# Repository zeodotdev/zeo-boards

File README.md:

# Zeo Boards

This is a repo of boards made with zeo made by the team and submitted by users.

- demo_board: The board made in the [walkthrough](https://youtu.be/U7OuzNha7m4?si=L84EUU4cbVrLih4U)
- zeo1_debvoard: 1inx1in sensor board built on the esp32c3: placed with ai + autorouted
- jared_tv_remote: Jared's universal TV remote, codename: "Bromote 9000"
- fpv_drone: PCB drone frame designed for DL2205-2300KV Motors. placed by hand + routed by hand
- zeo1.2_devboard: a more powerful 1inx1in sensor board build built on the esp32s3: placed + routed by hand
- zeo_compute_module: a compute module designed arounf the RK3588, in-progress

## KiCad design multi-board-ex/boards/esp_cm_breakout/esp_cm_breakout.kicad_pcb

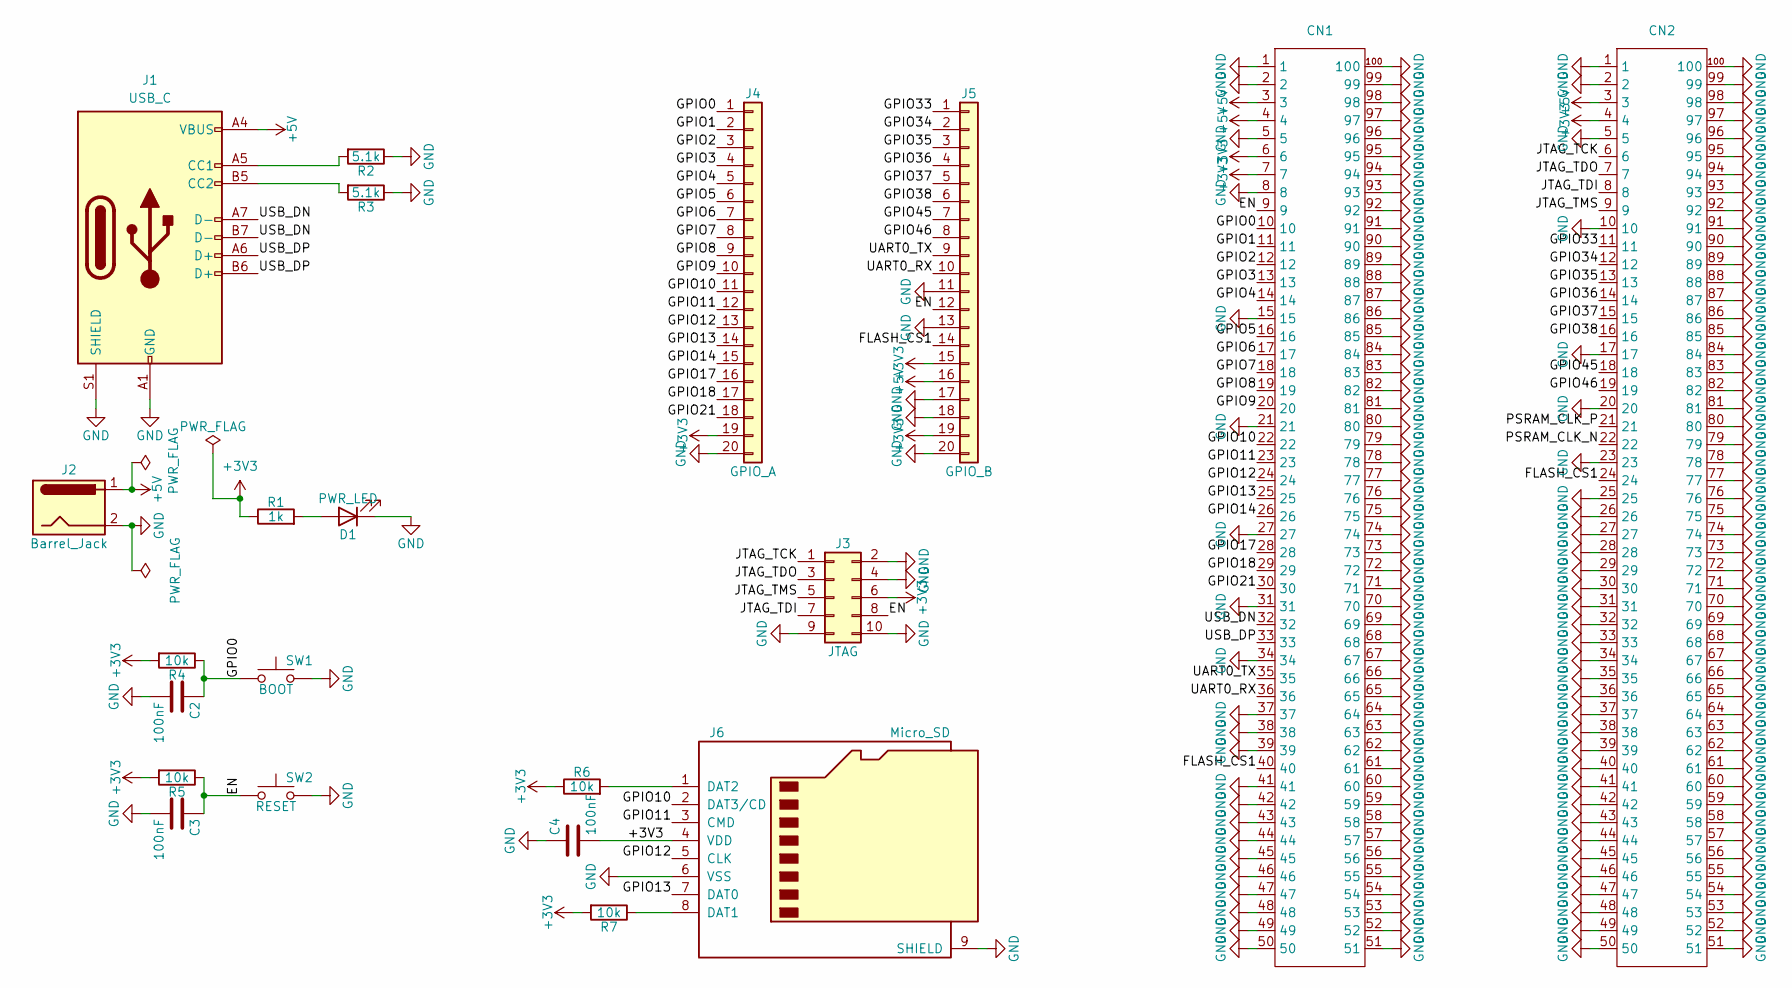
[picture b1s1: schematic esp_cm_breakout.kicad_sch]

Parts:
C2, C3, C4: 100nF; C_0603_1608Metric
CN1, CN2: CONN-SMD_DF40C-100DS-0.4V-51; Manufacturer Part DF40C-100DS-0.4V(51); LCSC Part Name PIN:100P 间距:0.4mm 立贴
D1: PWR_LED; LED_0603_1608Metric
J1: USB_C; USB_C_Receptacle_GCT_USB4085
J2: Barrel_Jack; BarrelJack_Horizontal
J3: JTAG; PinHeader_2x05_P2.54mm_Vertical
J4: GPIO_A; PinHeader_1x20_P2.54mm_Vertical
J5: GPIO_B; PinHeader_1x20_P2.54mm_Vertical
J6: Micro_SD; microSD_HC_Wuerth_693072010801
R1: 1k; R_0603_1608Metric
R2, R3: 5.1k; R_0603_1608Metric
R4, R5, R6, R7: 10k; R_0603_1608Metric
SW1: BOOT; SW_PUSH_6mm
SW2: RESET; SW_PUSH_6mm

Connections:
+3V3: C4.2, CN1.6, CN1.7, CN2.4, J3.6, J4.19, J5.15, J5.19, J6.4 (VDD_4), R1.1, R4.2, R5.2, R6.1, R7.2
+5V: CN1.3, CN1.4, CN2.3, J1.A4 (VBUS), J1.A9 (VBUS), J1.B4 (VBUS), J1.B9 (VBUS), J2.1, J5.16
/EN: C3.1, CN1.9, J3.8, J5.12, R5.1, SW2.1
/FLASH_CS1: CN1.40, CN2.24, J5.14
/GPIO0: C2.1, CN1.10, J4.1, R4.1, SW1.1
/GPIO1: CN1.11, J4.2
/GPIO2: CN1.12, J4.3
/GPIO3: CN1.13, J4.4
/GPIO4: CN1.14, J4.5
/GPIO5: CN1.16, J4.6
/GPIO6: CN1.17, J4.7
/GPIO7: CN1.18, J4.8
/GPIO8: CN1.19, J4.9
/GPIO9: CN1.20, J4.10
/GPIO10: CN1.22, J4.11, J6.2 (DAT3/CD_2)
/GPIO11: CN1.23, J4.12, J6.3 (CMD_3)
/GPIO12: CN1.24, J4.13, J6.5 (CLK_5)
/GPIO13: CN1.25, J4.14, J6.7 (DAT0_7)
/GPIO14: CN1.26, J4.15
/GPIO17: CN1.28, J4.16
/GPIO18: CN1.29, J4.17
/GPIO21: CN1.30, J4.18
/GPIO33: CN2.11, J5.1
/GPIO34: CN2.12, J5.2
/GPIO35: CN2.13, J5.3
/GPIO36: CN2.14, J5.4
/GPIO37: CN2.15, J5.5
/GPIO38: CN2.16, J5.6
/GPIO45: CN2.18, J5.7
/GPIO46: CN2.19, J5.8
/JTAG_TCK: CN2.6, J3.1
/JTAG_TDI: CN2.8, J3.7
/JTAG_TDO: CN2.7, J3.3
/JTAG_TMS: CN2.9, J3.5
/PSRAM_CLK_N: CN2.22
/PSRAM_CLK_P: CN2.21
/UART0_RX: CN1.36, J5.10
/UART0_TX: CN1.35, J5.9
/USB_DN: CN1.32, J1.A7 (D-), J1.B7 (D-)
/USB_DP: CN1.33, J1.A6 (D+), J1.B6 (D+)
GND: C2.2, C3.2, C4.1, CN1.1, CN1.2, CN1.5, CN1.8, CN1.15, CN1.21, CN1.27, CN1.31, CN1.34, CN1.37, CN1.38, CN1.39, CN1.41, CN1.42, CN1.43, CN1.44, CN1.45, CN1.46, CN1.47, CN1.48, CN1.49, CN1.50, CN1.51, CN1.52, CN1.53, CN1.54, CN1.55, CN1.56, CN1.57, CN1.58, CN1.59, CN1.60, CN1.61, CN1.62, CN1.63, CN1.64, CN1.65, CN1.66, CN1.67, CN1.68, CN1.69, CN1.70, CN1.71, CN1.72, CN1.73, CN1.74, CN1.75, CN1.76, CN1.77, CN1.78, CN1.79, CN1.80, CN1.81, CN1.82, CN1.83, CN1.84, CN1.85, CN1.86, CN1.87, CN1.88, CN1.89, CN1.90, CN1.91, CN1.92, CN1.93, CN1.94, CN1.95, CN1.96, CN1.97, CN1.98, CN1.99, CN1.100, CN2.1, CN2.2, CN2.5, CN2.10, CN2.17, CN2.20, CN2.23, CN2.25, CN2.26, CN2.27, CN2.28, CN2.29, CN2.30, CN2.31, CN2.32, CN2.33, CN2.34, CN2.35, CN2.36, CN2.37, CN2.38, CN2.39, CN2.40, CN2.41, CN2.42, CN2.43, CN2.44, CN2.45, CN2.46, CN2.47, CN2.48, CN2.49, CN2.50, CN2.51, CN2.52, CN2.53, CN2.54, CN2.55, CN2.56, CN2.57, CN2.58, CN2.59, CN2.60, CN2.61, CN2.62, CN2.63, CN2.64, CN2.65, CN2.66, CN2.67, CN2.68, CN2.69, CN2.70, CN2.71, CN2.72, CN2.73, CN2.74, CN2.75, CN2.76, CN2.77, CN2.78, CN2.79, CN2.80, CN2.81, CN2.82, CN2.83, CN2.84, CN2.85, CN2.86, CN2.87, CN2.88, CN2.89, CN2.90, CN2.91, CN2.92, CN2.93, CN2.94, CN2.95, CN2.96, CN2.97, CN2.98, CN2.99, CN2.100, D1.1 (K), J1.A1 (GND), J1.A12 (GND), J1.B1 (GND), J1.B12 (GND), J1.S1 (SHIELD), J2.2, J3.2, J3.4, J3.9, J3.10, J4.20, J5.11, J5.13, J5.17, J5.18, J5.20, J6.6 (VSS_6), J6.9 (SHIELD_9), J6.11 (SHIELD_9), R2.1, R3.1, SW1.2, SW2.2
unnamed: D1.2 (A), R1.2
unnamed: J1.A5 (CC1), R2.2
unnamed: J1.B5 (CC2), R3.2
unnamed: J6.8 (DAT1_8), R7.1
unnamed: J6.1 (DAT2_1), R6.2

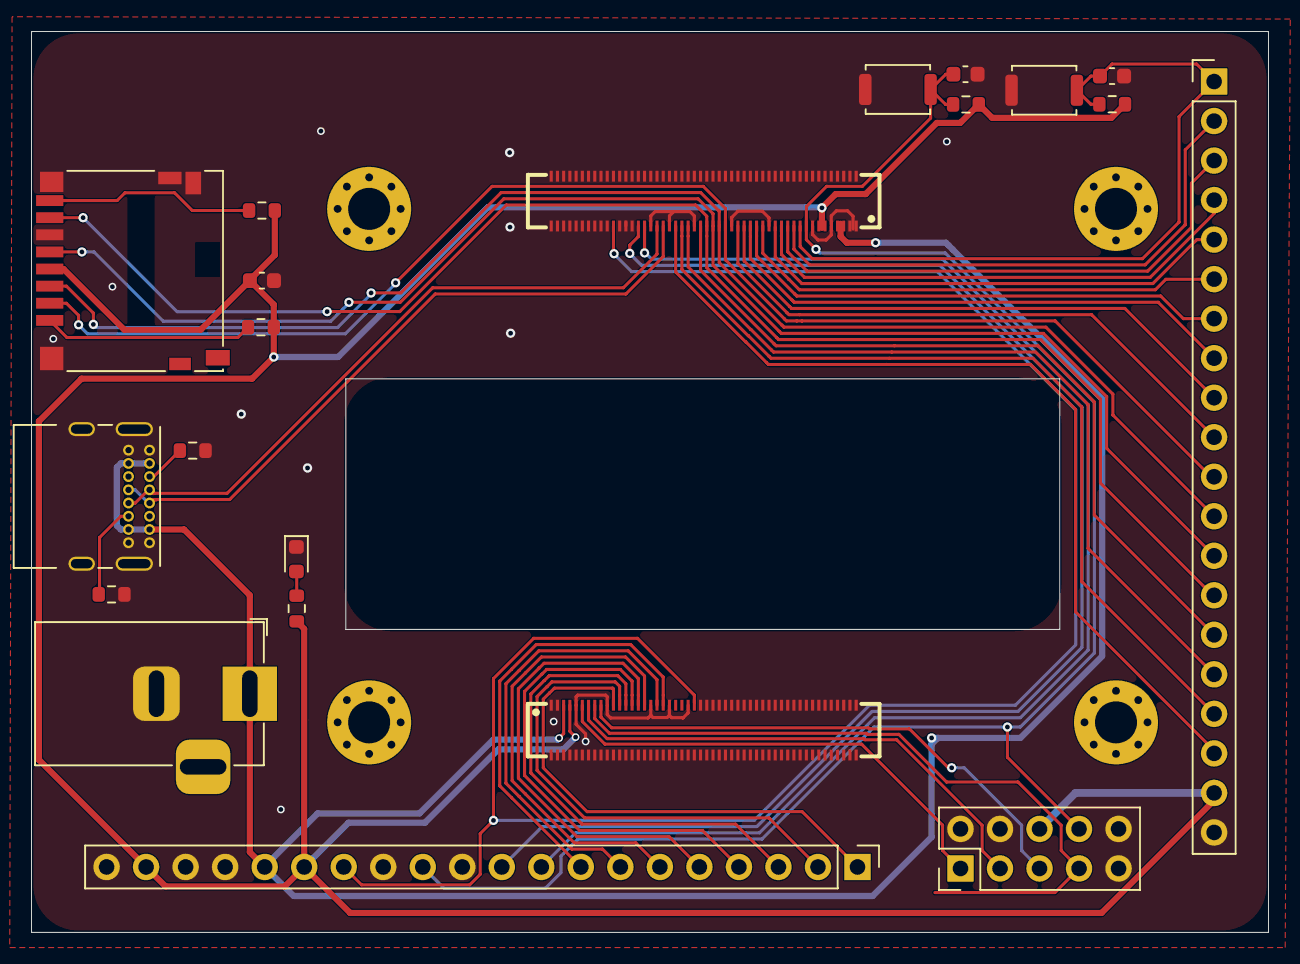
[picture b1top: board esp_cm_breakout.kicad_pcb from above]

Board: 2 copper layers, 79.5 x 57.9 mm, 21 parts (0 on the bottom side), 44 nets.

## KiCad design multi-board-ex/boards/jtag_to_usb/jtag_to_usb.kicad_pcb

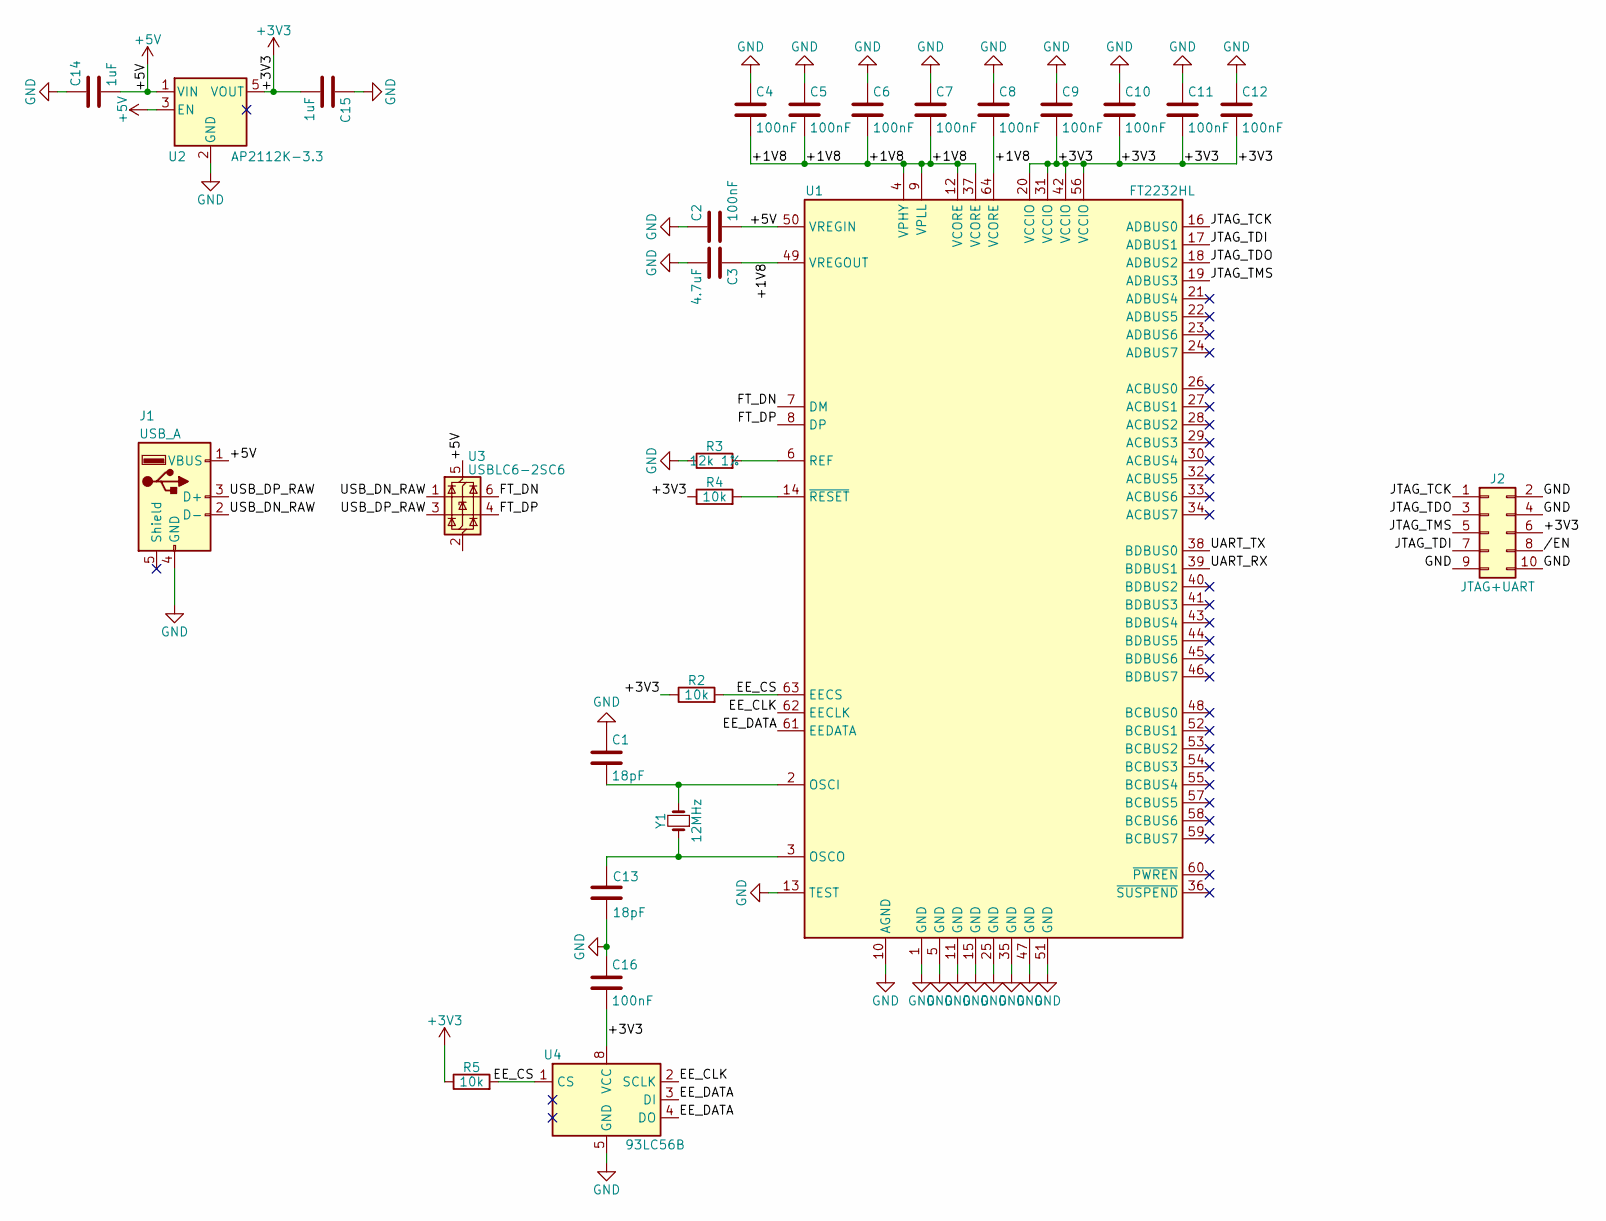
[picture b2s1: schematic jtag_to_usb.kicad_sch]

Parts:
C1, C13: 18pF; C_0402_1005Metric_Pad0.74x0.62mm_HandSolder
C2, C4, C5, C6, C7, C8, C9, C10, C11, C12, C16: 100nF; C_0402_1005Metric_Pad0.74x0.62mm_HandSolder
C3: 4.7uF; C_0805_2012Metric_Pad1.18x1.45mm_HandSolder
C14, C15: 1uF; C_0402_1005Metric_Pad0.74x0.62mm_HandSolder
J1: USB_A; USB_A_Molex_67643_Horizontal
J2: JTAG+UART; PinSocket_2x05_P2.54mm_Vertical
R2, R4, R5: 10k; R_0402_1005Metric_Pad0.72x0.64mm_HandSolder
R3: 12k 1%; R_0402_1005Metric_Pad0.72x0.64mm_HandSolder
U1: FT2232HL; LQFP-64_10x10mm_P0.5mm
U2: AP2112K-3.3; SOT-23-5
U3: USBLC6-2SC6; SOT-23-6
U4: 93LC56B; SOIC-8_3.9x4.9mm_P1.27mm
Y1: 12MHz; Crystal_SMD_3225-4Pin_3.2x2.5mm

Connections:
+3V3: C9.2, C10.2, C11.2, C12.2, C15.2, C16.2, J2.6, R2.1, R4.1, R5.1, U1.20 (VCCIO), U1.31 (VCCIO), U1.42 (VCCIO), U1.56 (VCCIO), U2.5 (VOUT), U4.8 (VCC)
+5V: C2.2, C14.2, J1.1 (VBUS), U1.50 (VREGIN), U2.1 (VIN), U2.3 (EN), U3.5 (VBUS)
/+1V8: C3.1, C4.2, C5.2, C6.2, C7.2, C8.2, U1.4 (VPHY), U1.9 (VPLL), U1.12 (VCORE), U1.37 (VCORE), U1.49 (VREGOUT), U1.64 (VCORE)
/EE_CLK: U1.62 (EECLK), U4.2 (SCLK)
/EE_CS: R2.2, R5.2, U1.63 (EECS), U4.1 (CS)
/EE_DATA: U1.61 (EEDATA), U4.3 (DI), U4.4 (DO)
/EN: J2.8
/FT_DN: U1.7 (DM), U3.6 (I/O1)
/FT_DP: U1.8 (DP), U3.4 (I/O2)
/JTAG_TCK: J2.1, U1.16 (ADBUS0)
/JTAG_TDI: J2.7, U1.17 (ADBUS1)
/JTAG_TDO: J2.3, U1.18 (ADBUS2)
/JTAG_TMS: J2.5, U1.19 (ADBUS3)
/UART_RX: U1.39 (BDBUS1)
/UART_TX: U1.38 (BDBUS0)
/USB_DN_RAW: J1.2 (D-), U3.1 (I/O1)
/USB_DP_RAW: J1.3 (D+), U3.3 (I/O2)
GND: C1.1, C2.1, C3.2, C4.1, C5.1, C6.1, C7.1, C8.1, C9.1, C10.1, C11.1, C12.1, C13.2, C14.1, C15.1, C16.1, J1.4 (GND), J2.2, J2.4, J2.9, J2.10, R3.1, U1.1 (GND), U1.5 (GND), U1.10 (AGND), U1.11 (GND), U1.13 (TEST), U1.15 (GND), U1.25 (GND), U1.35 (GND), U1.47 (GND), U1.51 (GND), U2.2 (GND), U4.5 (GND)
unnamed: C1.2, U1.2 (OSCI), Y1.2
unnamed: C13.1, U1.3 (OSCO), Y1.1
unnamed: R3.2, U1.6 (REF)
unnamed: R4.2, U1.14 (~RESET)

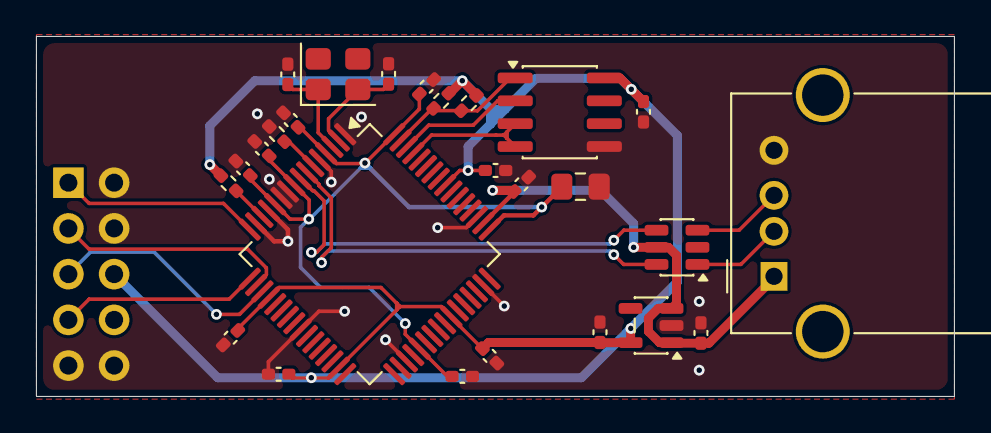
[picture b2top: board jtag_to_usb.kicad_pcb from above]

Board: 2 copper layers, 51.0 x 20.0 mm, 27 parts (1 on the bottom side), 19 nets.

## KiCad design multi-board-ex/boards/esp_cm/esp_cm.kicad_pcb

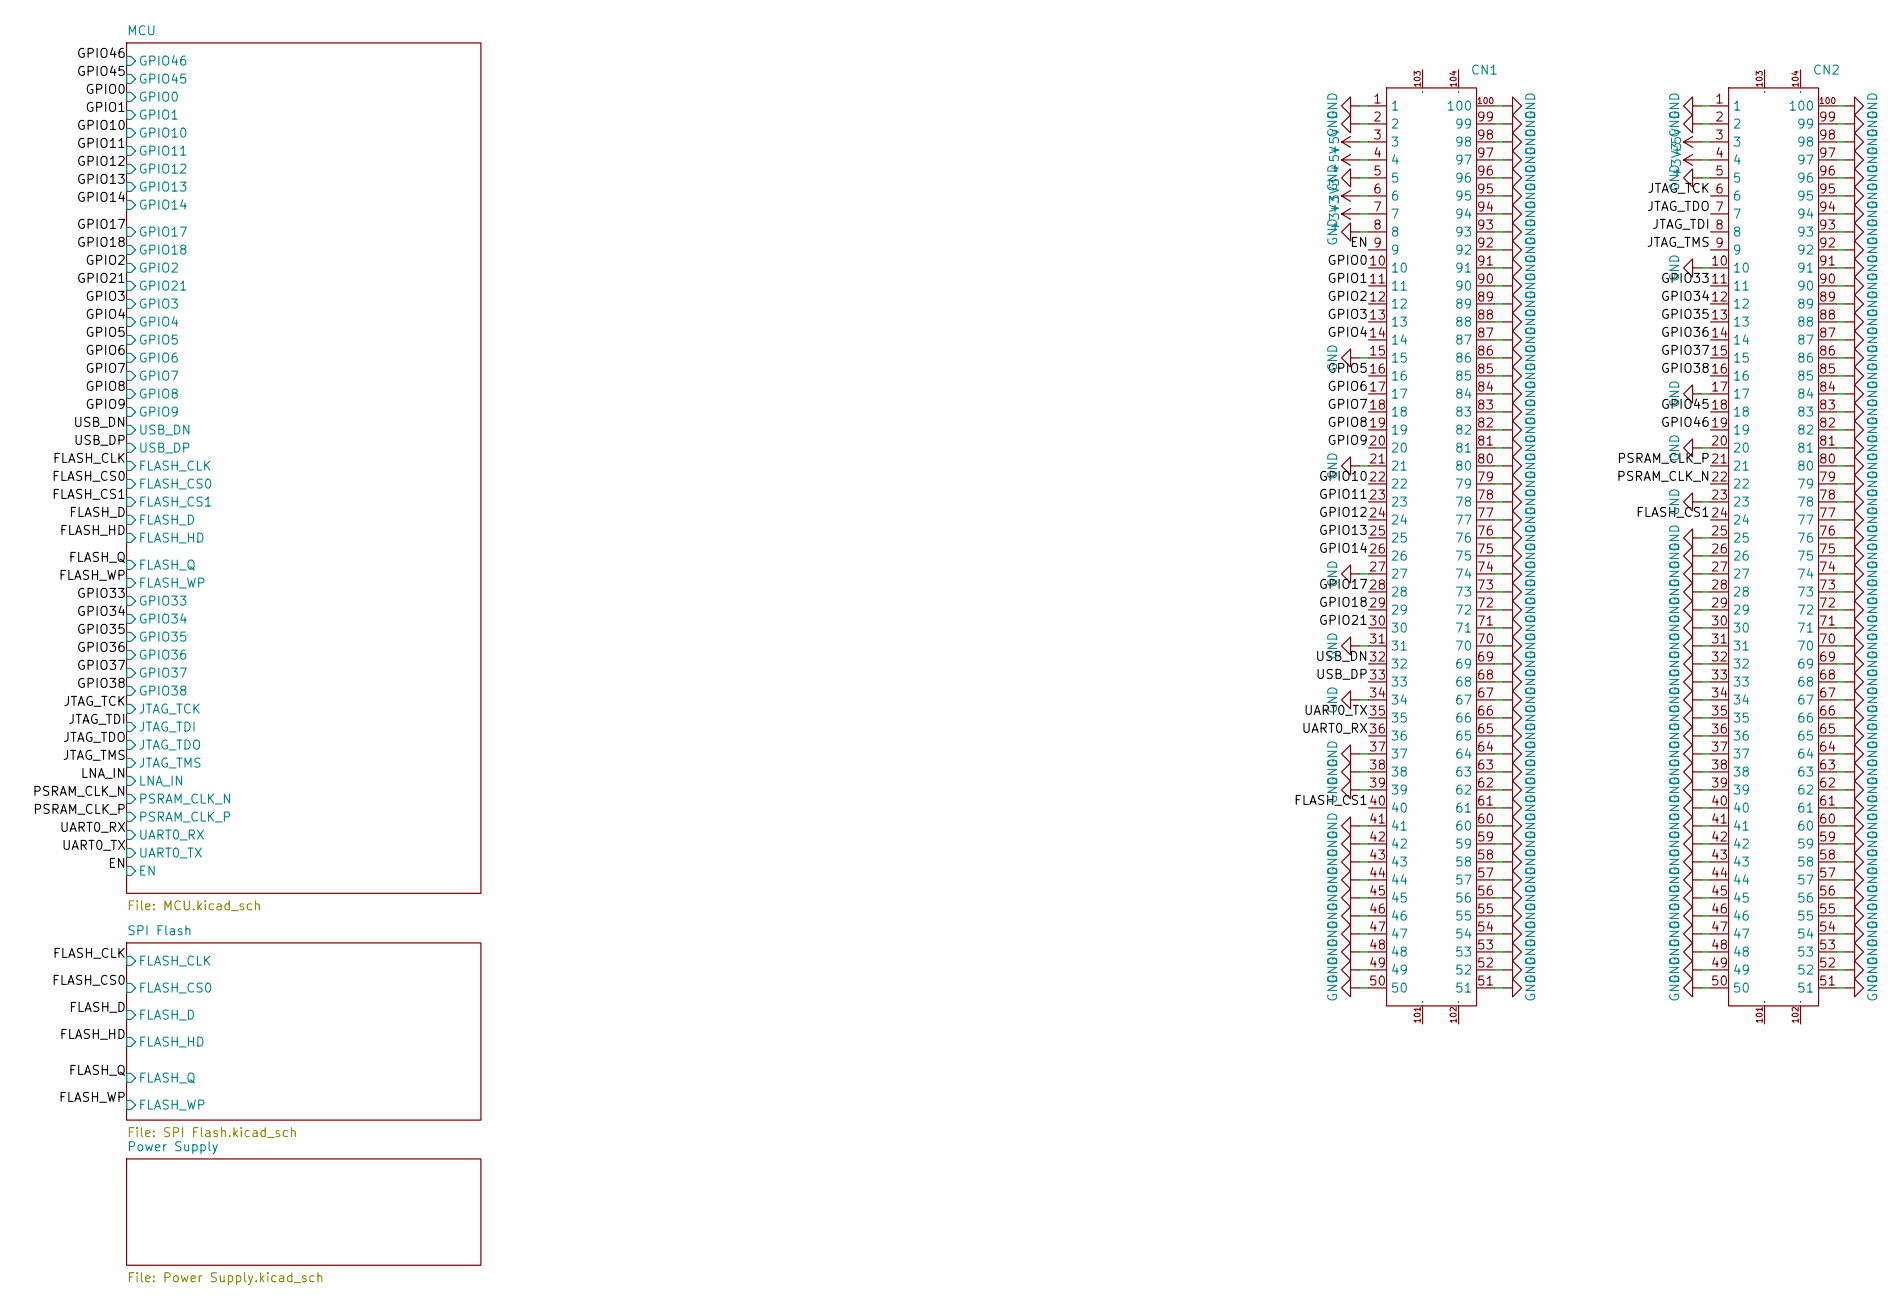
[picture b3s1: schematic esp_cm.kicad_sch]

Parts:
CN1, CN2: CONN-SMD_100P-P0.40_DF40C-100DP-0.4V-51; Manufacturer Part DF40C-100DP-0.4V(51); LCSC Part Name PIN:100P 间距:0.4mm 立贴

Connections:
/EN: CN1.9; also elsewhere on the board
/FLASH_CS1: CN1.40, CN2.24; also elsewhere on the board
/GPIO0: CN1.10; also elsewhere on the board
/GPIO1: CN1.11; also elsewhere on the board
/GPIO2: CN1.12; also elsewhere on the board
/GPIO3: CN1.13; also elsewhere on the board
/GPIO4: CN1.14; also elsewhere on the board
/GPIO5: CN1.16; also elsewhere on the board
/GPIO6: CN1.17; also elsewhere on the board
/GPIO7: CN1.18; also elsewhere on the board
/GPIO8: CN1.19; also elsewhere on the board
/GPIO9: CN1.20; also elsewhere on the board
/GPIO10: CN1.22; also elsewhere on the board
/GPIO11: CN1.23; also elsewhere on the board
/GPIO12: CN1.24; also elsewhere on the board
/GPIO13: CN1.25; also elsewhere on the board
/GPIO14: CN1.26; also elsewhere on the board
/GPIO17: CN1.28; also elsewhere on the board
/GPIO18: CN1.29; also elsewhere on the board
/GPIO21: CN1.30; also elsewhere on the board
/GPIO33: CN2.11; also elsewhere on the board
/GPIO34: CN2.12; also elsewhere on the board
/GPIO35: CN2.13; also elsewhere on the board
/GPIO36: CN2.14; also elsewhere on the board
/GPIO37: CN2.15; also elsewhere on the board
/GPIO38: CN2.16; also elsewhere on the board
/GPIO45: CN2.18; also elsewhere on the board
/GPIO46: CN2.19; also elsewhere on the board
/JTAG_TCK: CN2.6; also elsewhere on the board
/JTAG_TDI: CN2.8; also elsewhere on the board
/JTAG_TDO: CN2.7; also elsewhere on the board
/JTAG_TMS: CN2.9; also elsewhere on the board
/PSRAM_CLK_N: CN2.22; also elsewhere on the board
/PSRAM_CLK_P: CN2.21; also elsewhere on the board
/UART0_RX: CN1.36; also elsewhere on the board
/UART0_TX: CN1.35; also elsewhere on the board
/USB_DN: CN1.32; also elsewhere on the board
/USB_DP: CN1.33; also elsewhere on the board

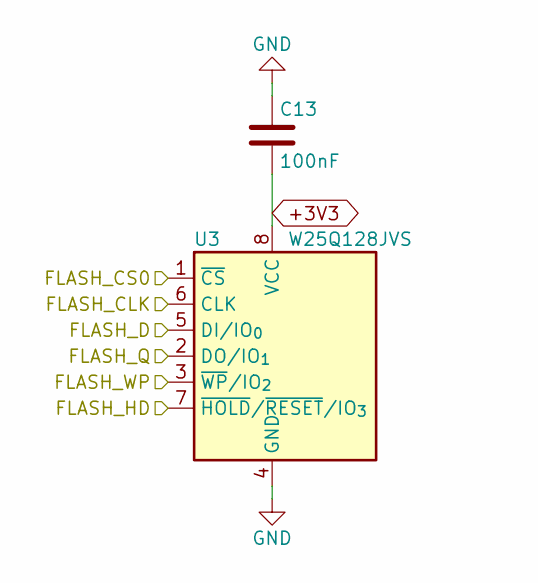
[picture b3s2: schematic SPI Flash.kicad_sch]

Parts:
C13: 100nF; C_0402_1005Metric
U3: W25Q128JVS; SOIC-8_5.3x5.3mm_P1.27mm

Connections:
/FLASH_CLK: U3.6 (CLK); also elsewhere on the board
/FLASH_CS0: U3.1 (~CS); also elsewhere on the board
/FLASH_D: U3.5 (DI/IO_{0}); also elsewhere on the board
/FLASH_HD: U3.7 (~HOLD/~RESET/IO_{3}); also elsewhere on the board
/FLASH_Q: U3.2 (DO/IO_{1}); also elsewhere on the board
/FLASH_WP: U3.3 (~WP/IO_{2}); also elsewhere on the board

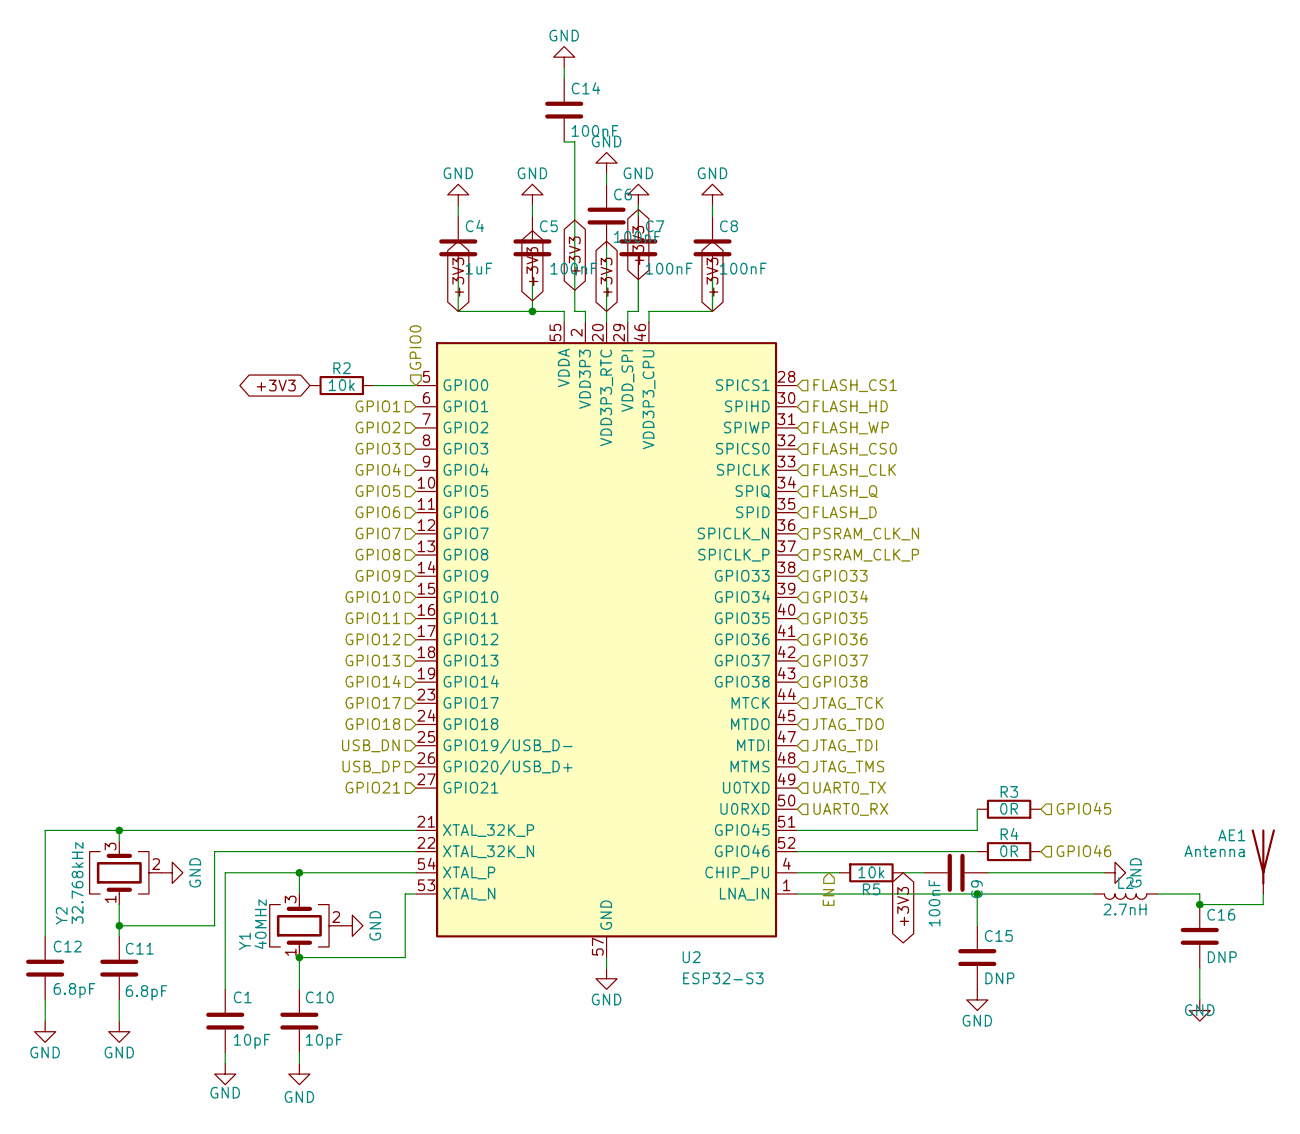
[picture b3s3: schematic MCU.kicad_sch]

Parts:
AE1: Antenna; Texas_SWRA117D_2.4GHz_Right
C1, C10: 10pF; C_0402_1005Metric
C4: 1uF; C_0402_1005Metric
C5, C6, C7, C8, C9, C14: 100nF; C_0402_1005Metric
C11, C12: 6.8pF; C_0402_1005Metric
C15, C16: DNP; C_0402_1005Metric
L2: 2.7nH; L_0402_1005Metric
R2, R5: 10k; R_0402_1005Metric
R3, R4: 0R; R_0402_1005Metric
U2: ESP32-S3; QFN-56-1EP_7x7mm_P0.4mm_EP4x4mm
Y1: 40MHz; Crystal_SMD_3225-4Pin_3.2x2.5mm
Y2: 32.768kHz; Crystal_SMD_3225-4Pin_3.2x2.5mm

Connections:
/EN: R5.2, U2.4 (CHIP_PU); also elsewhere on the board
/FLASH_CLK: U2.33 (SPICLK); also elsewhere on the board
/FLASH_CS0: U2.32 (SPICS0); also elsewhere on the board
/FLASH_CS1: U2.28 (SPICS1); also elsewhere on the board
/FLASH_D: U2.35 (SPID); also elsewhere on the board
/FLASH_HD: U2.30 (SPIHD); also elsewhere on the board
/FLASH_Q: U2.34 (SPIQ); also elsewhere on the board
/FLASH_WP: U2.31 (SPIWP); also elsewhere on the board
/GPIO0: R2.2, U2.5 (GPIO0); also elsewhere on the board
/GPIO1: U2.6 (GPIO1); also elsewhere on the board
/GPIO2: U2.7 (GPIO2); also elsewhere on the board
/GPIO3: U2.8 (GPIO3); also elsewhere on the board
/GPIO4: U2.9 (GPIO4); also elsewhere on the board
/GPIO5: U2.10 (GPIO5); also elsewhere on the board
/GPIO6: U2.11 (GPIO6); also elsewhere on the board
/GPIO7: U2.12 (GPIO7); also elsewhere on the board
/GPIO8: U2.13 (GPIO8); also elsewhere on the board
/GPIO9: U2.14 (GPIO9); also elsewhere on the board
/GPIO10: U2.15 (GPIO10); also elsewhere on the board
/GPIO11: U2.16 (GPIO11); also elsewhere on the board
/GPIO12: U2.17 (GPIO12); also elsewhere on the board
/GPIO13: U2.18 (GPIO13); also elsewhere on the board
/GPIO14: U2.19 (GPIO14); also elsewhere on the board
/GPIO17: U2.23 (GPIO17); also elsewhere on the board
/GPIO18: U2.24 (GPIO18); also elsewhere on the board
/GPIO21: U2.27 (GPIO21); also elsewhere on the board
/GPIO33: U2.38 (GPIO33); also elsewhere on the board
/GPIO34: U2.39 (GPIO34); also elsewhere on the board
/GPIO35: U2.40 (GPIO35); also elsewhere on the board
/GPIO36: U2.41 (GPIO36); also elsewhere on the board
/GPIO37: U2.42 (GPIO37); also elsewhere on the board
/GPIO38: U2.43 (GPIO38); also elsewhere on the board
/GPIO45: R3.2; also elsewhere on the board
/GPIO46: R4.2; also elsewhere on the board
/JTAG_TCK: U2.44 (MTCK); also elsewhere on the board
/JTAG_TDI: U2.47 (MTDI); also elsewhere on the board
/JTAG_TDO: U2.45 (MTDO); also elsewhere on the board
/JTAG_TMS: U2.48 (MTMS); also elsewhere on the board
/PSRAM_CLK_N: U2.36 (SPICLK_N); also elsewhere on the board
/PSRAM_CLK_P: U2.37 (SPICLK_P); also elsewhere on the board
/UART0_RX: U2.50 (U0RXD); also elsewhere on the board
/UART0_TX: U2.49 (U0TXD); also elsewhere on the board
/USB_DN: U2.25 (GPIO19/USB_D-); also elsewhere on the board
/USB_DP: U2.26 (GPIO20/USB_D+); also elsewhere on the board
unnamed: AE1.1 (A_1), C16.1, L2.1
unnamed: R3.1, U2.51 (GPIO45)
unnamed: R4.1, U2.52 (GPIO46)
unnamed: C15.1, L2.2, U2.1 (LNA_IN)
unnamed: C11.1, U2.22 (XTAL_32K_N), Y2.1
unnamed: C12.1, U2.21 (XTAL_32K_P), Y2.3
unnamed: C10.1, U2.53 (XTAL_N), Y1.1
unnamed: C1.1, U2.54 (XTAL_P), Y1.3

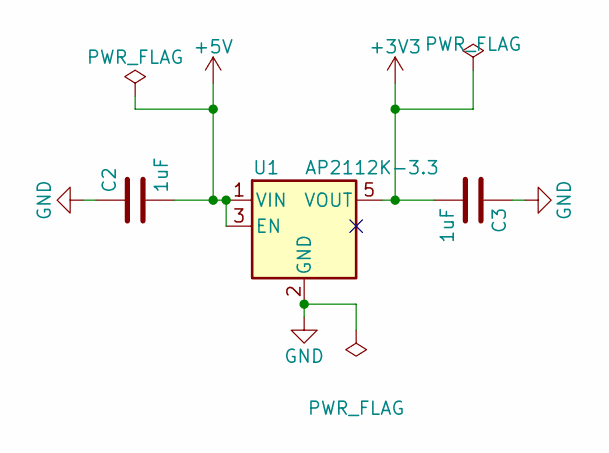
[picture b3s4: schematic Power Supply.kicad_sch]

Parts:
C2, C3: 1uF; C_0402_1005Metric
U1: AP2112K-3.3; SOT-23-5

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
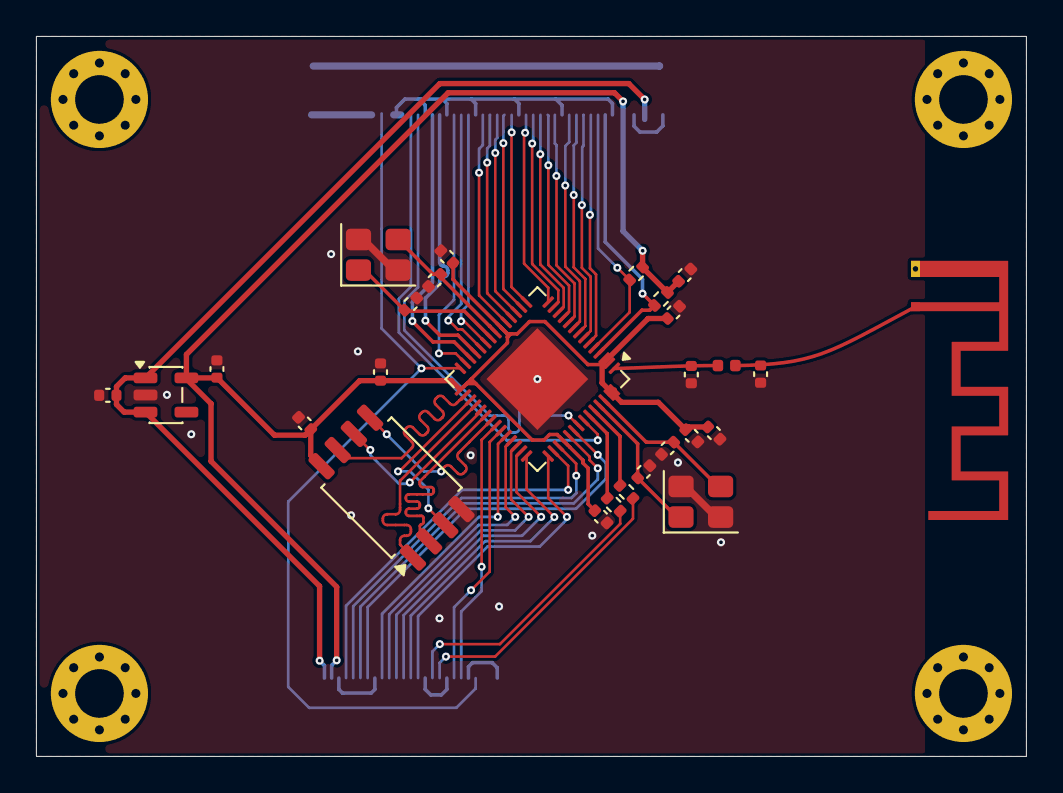
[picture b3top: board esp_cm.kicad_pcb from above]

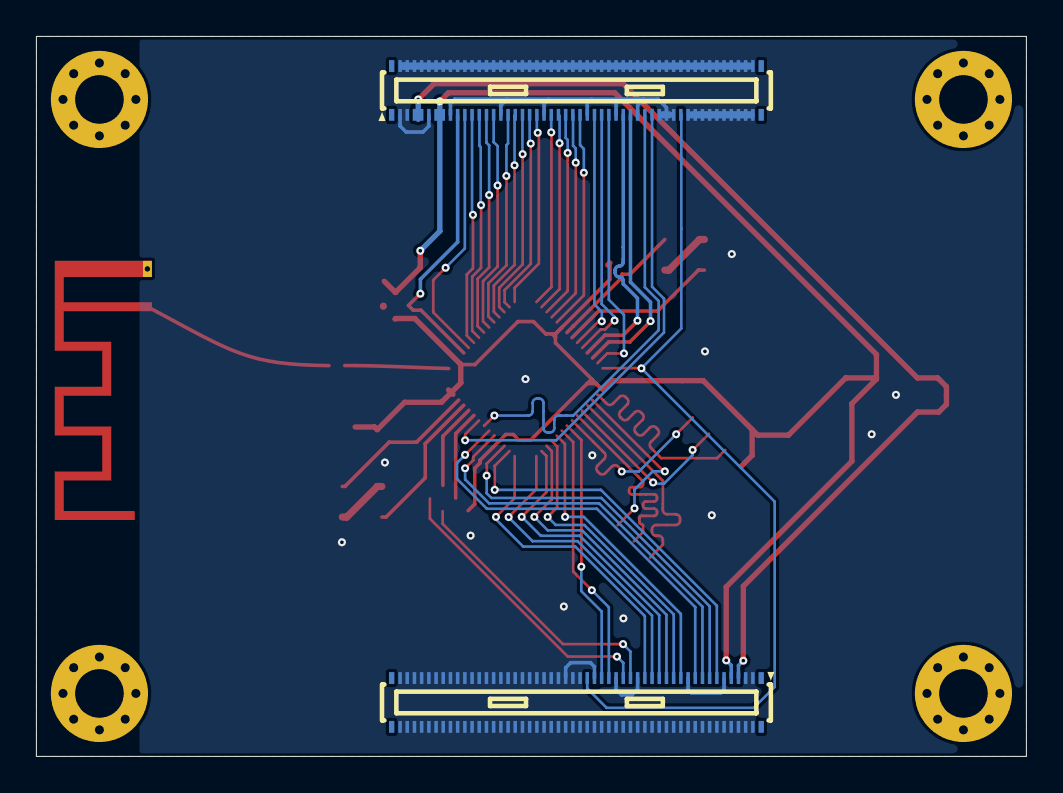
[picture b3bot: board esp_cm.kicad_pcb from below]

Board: 2 copper layers, 55.0 x 40.0 mm, 29 parts (2 on the bottom side), 55 nets.
